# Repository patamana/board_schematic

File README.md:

# パタマナボード 回路図・kicadデータ
パタマナボードの回路図やkicadデータです。

## パタマナボードの概要
XIAO用キーボード基板です。<br>
XIAOは無線接続ができて便利ですが、端子数が少なく、マトリクス構造にしてもOLEDを制御するピンなどが足りなくなってしまいます。<br>
シフトレジスタの74HC165を4つ実装することで、**XIAOの3ピンで32キーの読み取りに対応**しました。<br>
I2CによるOLED制御、TRRSジャックによる左右通信、充電用のPHコネクタやスライドスイッチが実装可能です。

## シフトレジスタの概要
XIAOのD1,D2,D3ピンが74HC165のLD,CK,QHに配線されています。<br>
LDをLOWにすることでシフトレジスタにロードされ、<br>
QHからSW0のHIGE/LOWが出力されます。<br>
CKが立ち上がるたびに出力信号がSW1,SW2...とシフトされていきます。

## ピン配置
XIAOのSDA,SCLピンがOLED用の端子のSDA,SCLに配線されています。

TRRSにはXIAOのTX,RXピンとUSBからの5Vが配線されており、左右でTXとRXが逆になっているので、TRRSジャックの実装位置を変えることで、UARTでの左右通信が可能です。

XIAOの裏面の+端子をパタマナボード裏面のBAT+端子に繋げ、スライドスイッチとPHコネクタを実装し、PHコネクタにリチウムイオンポリマーバッテリーを繋げることで充電が可能です。

バッテリーの電圧を200kΩ抵抗2つの直列で分圧した電圧がXIAOのD0ピンに印加されているので、電圧値を読み取ることでバッテリー残量がわかります。

D8,D9,D10ピンは未使用なので、自由に利用できます<br><br>

詳しい利用方法は[patamana.com](https://patamana.com)を参照してください。

Arduino IDE を用いる場合は、[patamana/keybard_firmware/simple_split_keyboard](https://github.com/patamana/keyboard_firmware/tree/main/simple_split_keyboard)のコードを参考にしてください。

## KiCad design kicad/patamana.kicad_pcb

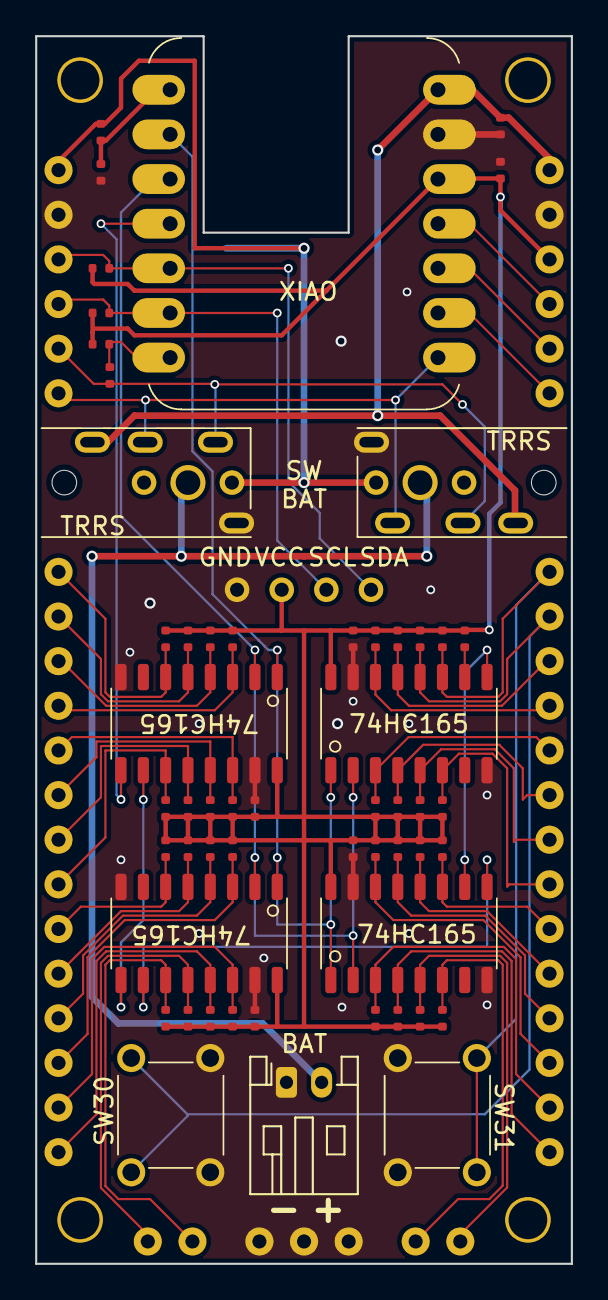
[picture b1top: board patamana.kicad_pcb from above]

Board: 2 copper layers, 30.5 x 69.8 mm, 59 parts (0 on the bottom side), 53 nets.

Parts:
C1, C2: 10u; 0402
C3, C4, C5, C6: 0.1u; 0402
J1, J2: TRRSJack; MJ-4PP-9
J3: Conn_01x02; JST_PH_S2B-PH-K_1x02_P2.00mm_Horizontal
R1, R35: 200k; 0402
R2, R3, R4, R5, R6, R7, R8, R9, R10, R11, R12, R13, R14, R15, R16, R17, R18, R19, R20, R21, R22, R23, R24, R25, R26, R27, R28, R29, R30, R31, R32, R33, R34: 33k; 0402
R36, R37, R38: 10k; 0402
R39: 100; 0402
SW1, SW2: SW_Push; Tactile_Switch_TVDP01
SW3, SW4: SW_DPDT_x2; SS-12D00-G5
U1: XIAO_ESP32S3
U2, U4, U5, U6: 74HC165; SOT109-1_SO16
U3: OLED(I2C); OLED_128x64_I2C
U7: patamana_0_4_out

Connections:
5V: C1.1, J1.R2, J2.R2, U1.14 (5V), U7.46
BAT+: R1.1, SW3.1 (A), SW4.1 (A), U7.35
BAT++: J3.2, SW3.2 (B), SW4.2 (B)
CK: U1.3 (D2/A2), U2.2 (CK), U4.2 (CK), U5.2 (CK), U6.2 (CK)
GND: C1.2, C2.2, C3.2, C4.2, C5.2, C6.2, J1.S, J2.S, J3.1, R35.2, SW1.2, SW2.2, U1.13 (GND), U2.8 (GND), U2.15 (CK_INH), U3.1 (GND), U4.8 (GND), U4.15 (CK_INH), U5.8 (GND), U5.15 (CK_INH), U6.8 (GND), U6.15 (CK_INH), U7.32, U7.33, U7.34, U7.36, U7.45
MISO: U1.10 (MISO/A9/D9), U7.42
MOSI: U1.11 (MOSI/A10/D10), U7.43
unnamed: R1.2, R35.1, U1.1 (D0/A0)
unnamed: U2.9 (QH), U4.10 (SI)
unnamed: U4.9 (QH), U5.10 (SI)
unnamed: U5.9 (QH), U6.10 (SI)
QH: U1.4 (D3/A3), U6.9 (QH)
RX: J1.R1, J2.T, U1.8 (RX/D7), U7.40
SCK: U1.9 (SCK/A8/D8), U7.41
SCL: R36.2, U1.6 (D5/A5/SCL), U3.3 (SCL), U7.38
SDA: R37.2, U1.5 (D4/A4/SDA), U3.4 (SDA), U7.37
SI: R2.2, U2.10 (SI)
SW0: R3.2, U6.6 (H), U7.0
SW1: R4.2, U6.5 (G), U7.1
SW2: R5.2, U6.4 (F), U7.2
SW3: R6.2, U6.3 (E), U7.3
SW4: R7.2, U6.14 (D), U7.4
SW5: R8.2, U6.13 (C), U7.5
SW6: R9.2, U6.12 (B), U7.6
SW7: R10.2, U6.11 (A), U7.7
SW8: R11.2, U5.6 (H), U7.8
SW9: R12.2, U5.5 (G), U7.9
SW10: R13.2, U5.4 (F), U7.10
SW11: R14.2, U5.3 (E), U7.11
SW12: R15.2, U5.14 (D), U7.12
SW13: R16.2, U5.13 (C), U7.13
SW14: R17.2, U5.12 (B), U7.14
SW15: R18.2, U5.11 (A), U7.15
SW16: R19.2, U4.6 (H), U7.16
SW17: R20.2, U4.5 (G), U7.17
SW18: R21.2, U4.4 (F), U7.18
SW19: R22.2, U4.3 (E), U7.19
SW20: R23.2, U4.14 (D), U7.20
SW21: R24.2, U4.13 (C), U7.21
SW22: R25.2, U4.12 (B), U7.22
SW23: R26.2, U4.11 (A), U7.23
SW24: R27.2, U2.6 (H), U7.24
SW25: R28.2, U2.5 (G), U7.25
SW26: R29.2, U2.4 (F), U7.26
SW27: R30.2, U2.3 (E), U7.27
SW28: R31.2, U2.14 (D), U7.28
SW29: R32.2, U2.13 (C), U7.29
SW30: R33.2, SW1.1, U2.12 (B), U7.30
SW31: R34.2, SW2.1, U2.11 (A), U7.31
S/~L: U1.2 (D1/A1), U2.1 (S/~L), U4.1 (S/~L), U5.1 (S/~L), U6.1 (S/~L)
TX: R38.1, R39.2, U1.7 (D6/TX)
TX_after_protection_resistance: J1.T, J2.R1, R39.1, U7.39
Vcc: C2.1, C3.1, C4.1, C5.1, C6.1, R2.1, R3.1, R4.1, R5.1, R6.1, R7.1, R8.1, R9.1, R10.1, R11.1, R12.1, R13.1, R14.1, R15.1, R16.1, R17.1, R18.1, R19.1, R20.1, R21.1, R22.1, R23.1, R24.1, R25.1, R26.1, R27.1, R28.1, R29.1, R30.1, R31.1, R32.1, R33.1, R34.1, R36.1, R37.1, R38.2, U1.12 (3V3), U2.16 (Vcc), U3.2 (Vcc), U4.16 (Vcc), U5.16 (Vcc), U6.16 (Vcc), U7.44

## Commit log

2024-03-08 追加:patamana_board_schematic.pdf ファイルの追加
2024-03-08 追加:kicad フォルダの追加
2024-03-08 追加:README.md ファイルの追加
2024-03-08 修正:README.mdの修正
2024-03-08 追加:README.mdにピン配置の説明を追加
2024-03-08 整理:名前の整理
